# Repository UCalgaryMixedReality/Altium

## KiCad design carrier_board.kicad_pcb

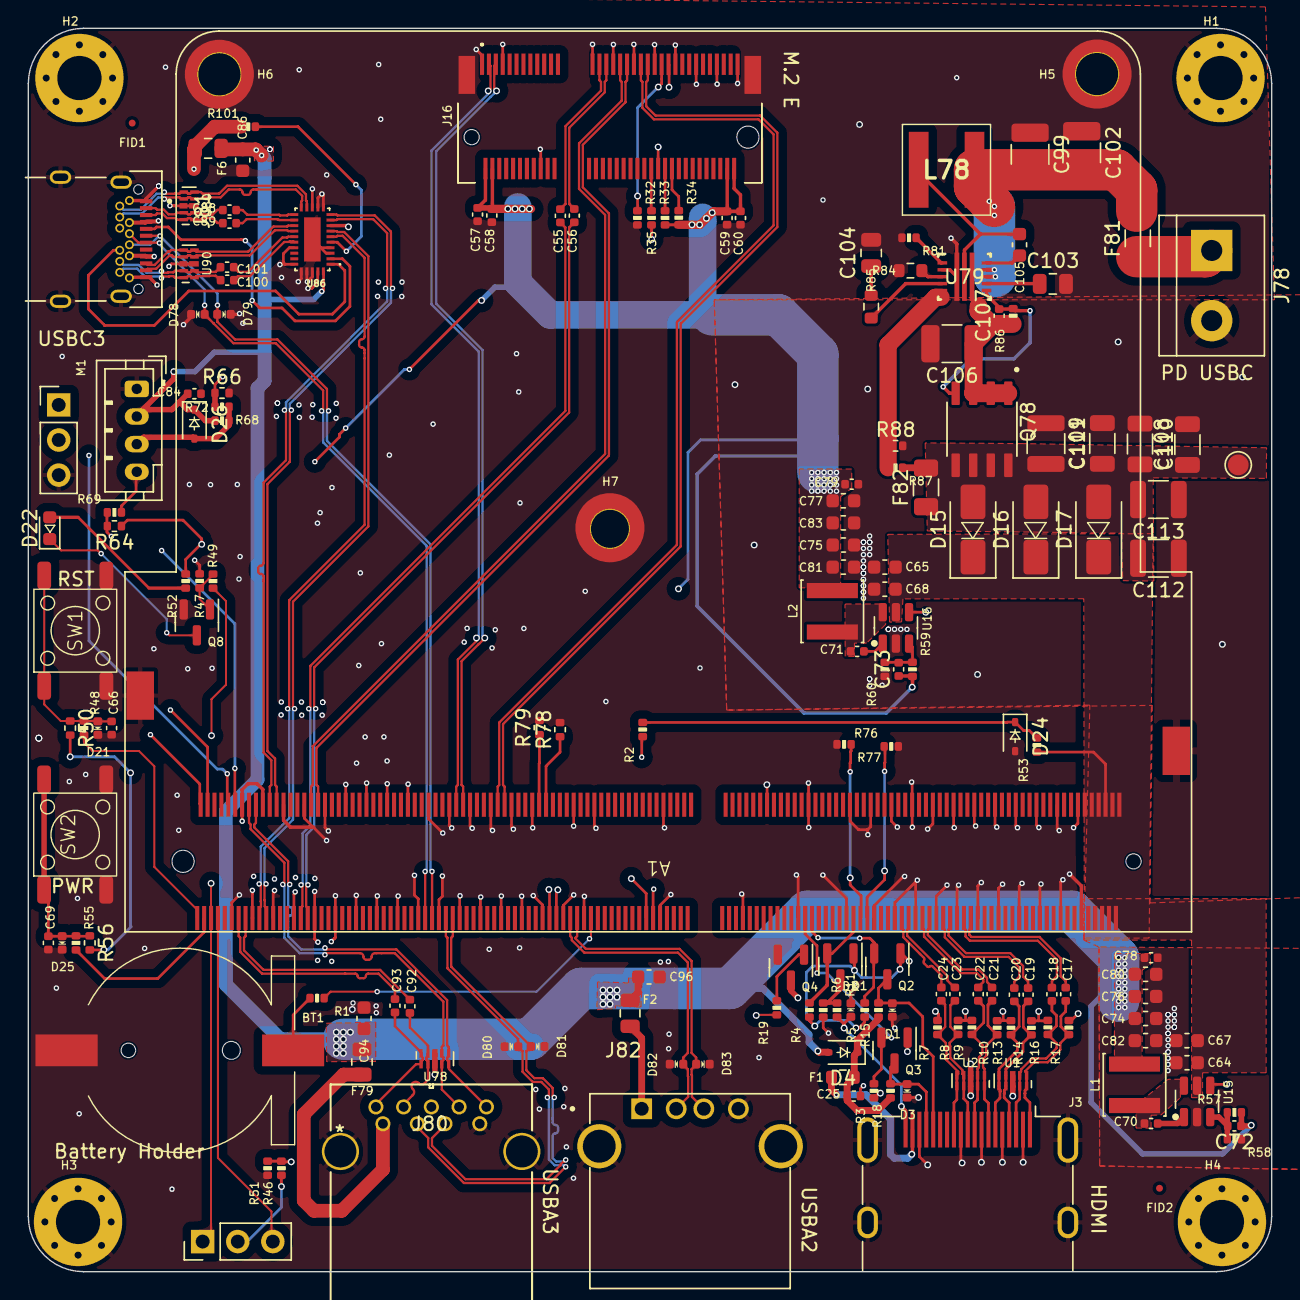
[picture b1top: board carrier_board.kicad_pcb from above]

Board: 4 copper layers, 90.0 x 90.0 mm, 175 parts (0 on the bottom side), 126 nets.

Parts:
A1: LattePanda_Mu; LattePanda_Module_H8.0mm_Horizontal
BT1: Battery_Cell; Battery_Holder_CR1220_S8411-45R
C17, C18, C19, C20, C21, C22, C23, C24, C25, C58, C60, C70, C71, C78, C79, C84, C88, C89, C92, C93, C100, C101: 100nF/50V; C_0402_1005Metric
C55, C56: 220nF/50V; C_0402_1005Metric
C57, C59: 10uF/10V; C_0402_1005Metric
C64, C65, C67, C68, C74, C75, C76, C77, C80, C81, C82, C83, C86, C94, C96: 22uF/10V; C_0603_1608Metric
C66, C69: 1uF/16V; C_0402_1005Metric
C72, C73: 12pF/50V; C_0402_1005Metric
C99, C102: 22uF; C_1210_3225Metric_Pad1.33x2.70mm_HandSolder
C103: 4.7uF; C_0805_2012Metric
C104: 1nF; C_0805_2012Metric
C105: 150nF; C_0603_1608Metric
C106: 10uF; C_1210_3225Metric_Pad1.33x2.70mm_HandSolder
C107: 22nF; C_0402_1005Metric
C108, C109, C110: 4.7uF; C_1206_3216Metric
C111, C112, C113: 22uF; C_1210_3225Metric
D1, D2, D3, D21, D25, D78, D79, D80, D81, D82, D83: ESD5V0B03; D_0402_1005Metric
D4, D26: 1N5819WS; D_SOD-323
D15, D16, D17: SS54; D_SMA
D22: LED_G; LED_0603_1608Metric
D24: 3V3 Izt=5mA; D_SOD-323
F1: 6V/50mA; R_0603_1608Metric
F2: 6V/1A; Fuse_0805_2012Metric
F6: 6V/2A; Fuse_0805_2012Metric
F79: 6V/2A; R_0805_2012Metric
F81: 32V/6A; Fuse_1206_3216Metric
F82: Fuse; Fuse_1206_3216Metric
FID1, FID2: Fiducial; Fiducial_0.5mm_Mask1mm
H1, H2, H3, H4: MountingHole_Pad; MountingHole_3.2mm_M3_Pad_Via
H5, H6: MountingHole_Pad; MountingHole_3mm_M2_Pad_TopOnly
H7: MountingHole_M2.0; MountingHole_2.7mm_M2_Pad_TopOnly
J1: Conn_01x03_Pin; PinHeader_1x03_P2.54mm_Vertical
J3: HDMI_A; HDMI_A_Molex_208658-1001_Horizontal
J16: Bus_M.2_Socket_E; PCIe_M.2_Connectors_P=0.5mm_H=4.2mm_KeyE
J78: Screw_Terminal_01x02; TerminalBlock_bornier-2_P5.08mm
J80: 0483930003; 484050003_MOL
J81: DX07S024JJ3R1300; AMPHENOL_GSB3CA11310DSHR
J82: USB-A1HSW6; OST_USB-A1HSW6
JP1: Jumper_3_Bridged12; PinHeader_1x03_P2.54mm_Vertical
L1, L2: 2.2uH/4.3A; L_Sunlord_SWPA4020S
L78: 560nF; XAL6030561MEB
M1: Fan_4pin; JST_PH_B4B-PH-K_1x04_P2.00mm_Vertical
Q1, Q8: 2N7002; SOT-23
Q2, Q3, Q4: 2SK3018; SOT-23
Q78: SI4427BDY-T1-E3; SOIC127P600X175-8N
R1, R11, R47: 1K/1%; R_0402_1005Metric
R2, R34, R35, R49, R50, R56, R58, R78, R79: 10K/1%; R_0402_1005Metric
R3, R5, R15, R18, R19, R52, R53: 2.2K/1%; R_0402_1005Metric
R4: 1M/1%; R_0402_1005Metric
R6, R59, R66, R68: 21.5K/1%; R_0402_1005Metric
R7, R8, R9, R10, R13, R14, R16, R17: 470R/1%; R_0402_1005Metric
R32, R33: 0R/1%; R_0402_1005Metric
R46, R48, R55, R69: 100R/1%; R_0402_1005Metric
R51, R76, R77: 100K/1%; R_0402_1005Metric
R57: 75K/1%; R_0402_1005Metric
R60, R64, R72: 4.7K/1%; R_0402_1005Metric
R81: 140k; R_0402_1005Metric
R84: 56.2k; R_0603_1608Metric
R85: 28.7k; R_0603_1608Metric
R86: 178k; R_0402_1005Metric
R87: 732k; R_0402_1005Metric
R88: 80.6k; R_0402_1005Metric
R101: 900k; R_0402_1005Metric
SW1, SW2: SW_Push; SW_Push_6x6x6
TP16: TestPoint; TestPoint_Pad_D1.5mm
U1, U2: TPAZ1023-04F; Diodes_UDFN-10_1.0x2.5mm_P0.5mm
U15, U16: SY8253ADC; TSOT-23-6
U78, U80, U90: ULC0524P; Diodes_UDFN-10_1.0x2.5mm_P0.5mm
U79: TPS61178RNWR; RNW0013A
U86: HD3SS3220IRNHT; QFN40P450X250X80-31N120X320

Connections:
5V_HDMI_VCC: C25.1, D4.1 (K), F1.1, R15.1, R18.1
+3V3: C57.2, C58.2, C59.2, C60.2, C73.1, C75.2, C77.2, C79.1, C81.2, C83.2, J16.2 (3.3V), J16.4 (3.3V), J16.72 (3.3V), J16.74 (3.3V), L2.2, Q1.1 (G), Q2.1 (G), Q3.1 (G), R3.1, R4.1, R5.1, R34.2, R35.1, R50.2, R52.2, R56.2, R59.2, R64.1, U86.8 (VCC33)
+5V: C72.1, C74.2, C76.2, C78.1, C80.2, C82.2, C84.1, C86.2, C94.2, C96.1, D4.2 (A), D26.1 (K), F2.1, F6.1, F79.1, L1.2, M1.2 (+), R57.2, R72.1, U86.30 (VDD5)
+12V: C108.1, C109.1, C110.2, C111.2, C112.2, C113.2, D15.2 (A), D16.2 (A), D17.2 (A), F82.1, F82.2, Q78.5, Q78.6, Q78.7, Q78.8, R87.1, TP16.1
+BATT: A1.115 (VBAT), R1.1
/Fan_Temp/FAN_1_PWM: A1.2 (FAN1_PWM), R64.2, R69.1
/Fan_Temp/FAN_1_TAC: A1.4 (FAN1_TAC), R66.1, R68.2
/HDMI/DDC_SCL: D1.2 (A2), J3.15 (SCL), Q2.3 (D), R15.2
/HDMI/DDC_SDA: D3.2 (A2), J3.16 (SDA), Q3.3 (D), R18.2
/HDMI/DDI_B_DDC_SCL: A1.171 (DDIB_DDC_SCL), Q2.2 (S), R5.2
/HDMI/DDI_B_DDC_SDA: A1.169 (DDIB_DDC_SDA), Q3.2 (S), R3.2
/HDMI/DDI_B_HPD: A1.183 (DDIB_HPD), Q1.2 (S), R4.2
/HDMI/DDI_B_TX0+: A1.217 (DDIB_TX0+), C17.1
/HDMI/DDI_B_TX0-: A1.215 (DDIB_TX0-), C18.1
/HDMI/DDI_B_TX1+: A1.211 (DDIB_TX1+), C19.1
/HDMI/DDI_B_TX1-: A1.209 (DDIB_TX1-), C20.1
/HDMI/DDI_B_TX2+: A1.205 (DDIB_TX2+), C21.1
/HDMI/DDI_B_TX2-: A1.203 (DDIB_TX2-), C22.1
/HDMI/DDI_B_TX3+: A1.199 (DDIB_TX3+), C23.1
/HDMI/DDI_B_TX3-: A1.197 (DDIB_TX3-), C24.1
/HDMI/HPD: D2.2 (A2), J3.19 (HPD), R11.2
/HDMI/TMDS_CK+: C23.2, J3.10 (CK+), R8.1, U2.4, U2.7 (NC)
/HDMI/TMDS_CK-: C24.2, J3.12 (CK-), R7.1, U2.5, U2.6 (NC)
/HDMI/TMDS_D0+: C21.2, J3.7 (D0+), R10.1, U2.1, U2.10 (NC)
/HDMI/TMDS_D0-: C22.2, J3.9 (D0-), R9.1, U2.2, U2.9 (NC)
/HDMI/TMDS_D1+: C19.2, J3.4 (D1+), R14.1, U1.4, U1.7 (NC)
/HDMI/TMDS_D1-: C20.2, J3.6 (D1-), R13.1, U1.5, U1.6 (NC)
/HDMI/TMDS_D2+: C17.2, J3.1 (D2+), R17.1, U1.1, U1.10 (NC)
/HDMI/TMDS_D2-: C18.2, J3.3 (D2-), R16.1, U1.2, U1.9 (NC)
/LattePanda Module/HSIO_0_TX+: A1.13 (HSIO0_TX+), C93.1
/LattePanda Module/HSIO_0_TX-: A1.15 (HSIO0_TX-), C92.1
/LattePanda Module/HSIO_1_TX+: A1.19 (HSIO1_TX+), U86.6 (TXP)
/LattePanda Module/HSIO_1_TX-: A1.21 (HSIO1_TX-), U86.7 (TXN)
/LattePanda Module/HSIO_3_RX+: A1.34 (HSIO3_RX+), J16.41 (PERp0)
/LattePanda Module/HSIO_3_RX-: A1.36 (HSIO3_RX-), J16.43 (PERn0)
/LattePanda Module/HSIO_3_TX+: A1.31 (HSIO3_TX+), C55.1
/LattePanda Module/HSIO_3_TX-: A1.33 (HSIO3_TX-), C56.1
/LattePanda Module/REFCLK3+: A1.88 (REFCLK3+), J16.47 (REFCLKp0)
/LattePanda Module/REFCLK3-: A1.90 (REFCLK3-), J16.49 (REFCLKn0)
/LattePanda Module/SLS_S3: A1.7 (SLS_S3), JP1.3 (B)
/LattePanda Module/SUSCLK_WIFI: A1.131 (SUSCLK), R33.2
/LattePanda Module/USB_2_P7+: A1.76 (USB2_P7+), J16.3 (USB_D+)
/LattePanda Module/USB_2_P7-: A1.78 (USB2_P7-), J16.5 (USB_D-)
/LattePanda Module/~PWR_SW: A1.1 (~PWRBTN), R48.2
/LattePanda Module/~RST_SW: A1.3 (~RSTBTN), R55.2
/M.2 E&M Key/CON_PCIE_TX_0+: C55.2, J16.35 (PETp0)
/M.2 E&M Key/CON_PCIE_TX_0-: C56.2, J16.37 (PETn0)
/M.2 E&M Key/~CLKREQE: J16.53 (~CLKREQ0), R32.1
/PSU/PWR_EN: R46.2, R51.2, U15.4 (EN), U16.4 (EN)
/USB2.0&USB3.0/CON_USB1_D_N: A1.109 (USB2_P5-), D82.2 (A2), J82.2 (D-)
/USB2.0&USB3.0/CON_USB1_D_P: A1.111 (USB2_P5+), D83.2 (A2), J82.3 (D+)
/USB2.0&USB3.0/CON_USB3_D_N: A1.73 (USB2_P2-), D80.2 (A2), J80.2 (D-)
/USB2.0&USB3.0/CON_USB3_D_P: A1.75 (USB2_P2+), D81.2 (A2), J80.3 (D+)
/USB2.0&USB3.0/CON_USB3_SSRX_N: A1.18 (HSIO0_RX-), J80.5 (STDA_SSRX-), U78.5, U78.6 (NC)
/USB2.0&USB3.0/CON_USB3_SSRX_P: A1.16 (HSIO0_RX+), J80.6 (STDA_SSRX+), U78.4, U78.7 (NC)
/USB2.0&USB3.0/CON_USB3_SSTX_N: C92.2, J80.8 (STDA_SSTX-), U78.2, U78.9 (NC)
/USB2.0&USB3.0/CON_USB3_SSTX_P: C93.2, J80.9 (STDA_SSTX+), U78.1, U78.10 (NC)
/USB2.0&USB3.0/CON_USB4_D_N: A1.67 (USB2_P1-), D78.2 (A2), J81.A7 (DA-), J81.B7 (DB-)
/USB2.0&USB3.0/CON_USB4_D_P: A1.69 (USB2_P1+), D79.2 (A2), J81.A6 (DA+), J81.B6 (DB+)
/USB2.0&USB3.0/CON_USB4_SSRX_N: A1.24 (HSIO1_RX-), U86.10 (RXN)
/USB2.0&USB3.0/CON_USB4_SSRX_P: A1.22 (HSIO1_RX+), U86.9 (RXP)
/USB2.0&USB3.0/CON_USBC_SSRX1_N: J81.B11 (RX1+), U80.5, U80.6 (NC), U86.14 (RX1N)
/USB2.0&USB3.0/CON_USBC_SSRX1_P: J81.B10 (RX1-), U80.4, U80.7 (NC), U86.15 (RX1P)
/USB2.0&USB3.0/CON_USBC_SSRX2_N: J81.A10 (RX2-), U86.18 (RX2N), U90.5, U90.6 (NC)
/USB2.0&USB3.0/CON_USBC_SSRX2_P: J81.A11 (RX2+), U86.19 (RX2P), U90.4, U90.7 (NC)
/USB2.0&USB3.0/CON_USBC_SSTX1_N: C88.1, J81.A2 (TX1+), U80.2, U80.9 (NC)
/USB2.0&USB3.0/CON_USBC_SSTX1_P: C89.1, J81.A3 (TX1-), U80.1, U80.10 (NC)
/USB2.0&USB3.0/CON_USBC_SSTX2_N: C101.2, J81.B3 (TX2-), U90.2, U90.9 (NC)
/USB2.0&USB3.0/CON_USBC_SSTX2_P: C100.2, J81.B2 (TX2+), U90.1, U90.10 (NC)
/~PLT_RST: A1.105 (~PLTRST), J16.52 (~PERST0)
/~PWR_LED/~PSON: A1.5 (SLS_S0), JP1.1 (A), R19.1, R47.1
/~WAKE: A1.103 (~WAKE), J16.55 (~PEWAKE0)
GND: A1.11 (GND), A1.14 (GND), A1.17 (GND), A1.20 (GND), A1.23 (GND), A1.26 (GND), A1.29 (GND), A1.32 (GND), A1.35 (GND), A1.38 (GND), A1.41 (GND), A1.44 (GND), A1.47 (GND), A1.50 (GND), A1.53 (GND), A1.56 (GND), A1.59 (GND), A1.62 (GND), A1.65 (GND), A1.68 (GND), A1.71 (GND), A1.74 (GND), A1.77 (GND), A1.80 (GND), A1.83 (GND), A1.86 (GND), A1.89 (GND), A1.92 (GND), A1.95 (GND), A1.98 (GND), A1.101 (GND), A1.107 (GND), A1.110 (GND), A1.113 (GND), A1.116 (GND), A1.135 (GND), A1.136 (GND), A1.151 (GND), A1.158 (GND), A1.167 (GND), A1.170 (GND), A1.181 (GND), A1.182 (GND), A1.188 (GND), A1.189 (GND), A1.194 (GND), A1.195 (GND), A1.200 (GND), A1.201 (GND), A1.206 (GND), A1.207 (GND), A1.212 (GND), A1.213 (GND), A1.218 (GND), A1.219 (GND), A1.224 (GND), A1.225 (GND), A1.230 (GND), A1.231 (GND), A1.236 (GND), A1.237 (GND), A1.242 (GND), A1.243 (GND), A1.248 (GND), A1.249 (GND), A1.MP (Mountinge_Pads), BT1.2 (-), C25.2, C57.1, C58.1, C59.1, C60.1, C64.1, C65.1, C66.2, C67.1, C68.1, C69.2, C74.1, C75.1, C76.1, C77.1, C78.2, C79.2, C80.1, C81.1, C82.1, C83.1, C84.2, C86.1, C94.1, C96.2, C99.1, C102.1, C103.2, C104.2, C106.2, C108.2, C109.2, C110.1, C111.1, C112.1, C113.1, D1.1 (A1), D2.1 (A1), D3.1 (A1), D21.1 (A1), D24.2 (A), D25.1 (A1), D78.1 (A1), D79.1 (A1), D80.1 (A1), D81.1 (A1), D82.1 (A1), D83.1 (A1), H1.1, H2.1, H3.1, H4.1, H5.1, H6.1, H7.1, J1.3, J3.2 (D2S), J3.5 (D1S), J3.8 (D0S), J3.11 (CKS), J3.17 (GND), J3.SH, J16.1 (GND), J16.7 (GND), J16.18 (GND), J16.33 (GND), J16.39 (GND), J16.45 (GND), J16.51 (GND), J16.57 (GND), J16.63 (GND), J16.69 (GND), J16.75 (GND), J16.MP1, J16.MP2, J78.2, J80.4 (GND), J80.7 (GND_DRAIN), J80.10, J80.11, J81.A1 (GNDA), J81.A12 (GNDA__1), J81.B1 (GNDB), J81.B12 (GNDB__1), J81.SH1, J81.SH3, J81.SH4, J82.4 (GND), M1.1 (-), Q4.2 (S), Q8.2 (S), R6.2, R32.2, R49.1, R51.1, R58.1, R60.1, R66.2, R76.2, R77.2, R78.2, R79.2, R81.2, R84.2, R88.2, SW1.2, SW2.2, U1.3 (VSS), U1.8 (VSS), U2.3 (VSS), U2.8 (VSS), U15.2 (GND), U16.2 (GND), U78.3 (VSS), U78.8 (VSS), U79.2 (AGND), U79.6 (PGND), U80.3 (VSS), U80.8 (VSS), U86.3 (CURRENT_MODE), U86.4 (PORT), U86.11 (DIR), U86.12 (~ENN_MUX), U86.13 (GND), U86.22 (ADDR), U86.25 (SDA/OUT1), U86.26 (SCL/OUT2), U86.27 (ID), U86.28 (GND__1), U86.29 (~ENN_CC), U86.31 (EXP_PAD), U90.3 (VSS), U90.8 (VSS)
unnamed: A1.12 (SIO_UART_RX), J1.2
unnamed: A1.10 (SIO_UART_TX), J1.1
unnamed: A1.187 (TCP0_HPD), R76.1
unnamed: A1.185 (TCP1_HPD), R77.1
unnamed: A1.133 (~BIOS_SEL), R2.1
unnamed: A1.100 (~CLKREQ3), R79.1
unnamed: A1.102 (~CLKREQ4), R78.1
unnamed: BT1.1 (+), R1.2
unnamed: C104.1, R85.2
unnamed: C66.1, D21.2 (A2), R48.1, R50.1, SW1.1
unnamed: D22.2 (A), R52.1
unnamed: D22.1 (K), Q8.3 (D)
unnamed: C69.1, D25.2 (A2), R55.1, R56.1, SW2.1
unnamed: D26.2 (A), M1.3 (Tacho), R68.1, R72.2
unnamed: F1.2, J3.18 (+5V)
unnamed: J16.50 (SUSCLK), R33.1
unnamed: J16.56 (~W_DISABLE1), R34.1
unnamed: J16.54 (~W_DISABLE2), R35.2
unnamed: F81.1, J78.1
unnamed: F79.2, J80.1 (VBUS)
unnamed: F6.2, J81.A4 (A_VBUS), J81.A9 (A_VBUS__1), J81.B4 (B_VBUS), J81.B9 (B_VBUS__1), R101.1
unnamed: J81.A5 (CC1), U86.2 (CC1)
unnamed: J81.B5 (CC2), U86.1 (CC2)
unnamed: F2.2, J82.1 (VBUS)
unnamed: JP1.2 (C), R46.1
unnamed: M1.4 (PWM), R69.2
unnamed: Q1.3 (D), R6.1, R11.1
unnamed: Q4.3 (D), R7.2, R8.2, R9.2, R10.2, R13.2, R14.2, R16.2, R17.2
unnamed: Q4.1 (G), R19.2
unnamed: Q8.1 (G), R47.2, R49.2
unnamed: C70.2, U15.1 (BOOST)
unnamed: C72.2, R57.1, R58.2, U15.3 (FB)
unnamed: C70.1, L1.1, U15.6 (SW)
unnamed: C71.2, U16.1 (BOOST)
unnamed: C73.2, R59.1, R60.2, U16.3 (FB)
unnamed: C71.1, L2.1, U16.6 (SW)
unnamed: C105.2, U79.13 (BST)
unnamed: R85.1, U79.4 (COMP)
unnamed: C107.2, Q78.4, R86.2, U79.9 (DISDRV)
unnamed: C99.2, C102.2, F81.2, L78.1, U79.11 (EN), U79.12 (VIN)
unnamed: R87.2, R88.1, U79.5 (FB)
unnamed: R81.1, U79.1 (FREQ_SYNC)
unnamed: R84.1, U79.3 (ILIMIT)
unnamed: C105.1, L78.2, U79.7 (SW)
unnamed: C103.1, U79.10 (VCC)
unnamed: C106.1, C107.1, Q78.1, Q78.2, Q78.3, R86.1, U79.8 (VOUT)
unnamed: C88.2, U86.16 (TX1N)
unnamed: C89.2, U86.17 (TX1P)
unnamed: C101.1, U86.20 (TX2N)
unnamed: C100.1, U86.21 (TX2P)
unnamed: R101.2, U86.5 (VBUS_DET)
VDC: A1.250 (VIN), A1.251 (VIN), A1.252 (VIN), A1.253 (VIN), A1.254 (VIN), A1.255 (VIN), A1.256 (VIN), A1.257 (VIN), A1.258 (VIN), A1.259 (VIN), A1.260 (VIN), C64.2, C65.2, C67.2, C68.2, D15.1 (K), D16.1 (K), D17.1 (K), R53.1, U15.5 (VIN), U16.5 (VIN)
VPullup: D24.1 (K), R2.2, R53.2

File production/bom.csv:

Designator,Footprint,Quantity,Value,LCSC Part #
A1,LattePanda_Module_H8.0mm_Horizontal,1,LattePanda_Mu,
BT1,Battery_Holder_CR1220_S8411-45R,1,Battery_Cell,
"C100, C101, C17, C18, C19, C20, C21, C22, C23, C24, C25, C58, C60, C70, C71, C78, C79, C84, C88, C89, C92, C93",0402,22,100nF/50V,
"C102, C111, C112, C113, C99",1210,5,22uF,
C103,0805,1,4.7uF,
C104,0805,1,1nF,
C105,0603,1,150nF,
C106,1210,1,10uF,
C107,0402,1,22nF,
"C108, C109, C110",1206,3,4.7uF,
"C55, C56",0402,2,220nF/50V,
"C57, C59",0402,2,10uF/10V,
"C64, C65, C67, C68, C74, C75, C76, C77, C80, C81, C82, C83, C86, C94, C96",0603,15,22uF/10V,
"C66, C69",0402,2,1uF/16V,
"C72, C73",0402,2,12pF/50V,
"D1, D2, D21, D25, D3, D78, D79, D80, D81, D82, D83",0402,11,ESD5V0B03,
"D15, D16, D17",D_SMA,3,SS54,
D22,0603,1,LED_G,
D24,D_SOD-323,1,3V3 Izt=5mA,
"D26, D4",D_SOD-323,2,1N5819WS,
F1,0603,1,6V/50mA,
F2,0805,1,6V/1A,
"F6, F79",0805,2,6V/2A,
F81,1206,1,32V/6A,
F82,1206,1,Fuse,
"H5, H6",MountingHole_3mm_M2_Pad_TopOnly,2,MountingHole_Pad,
H7,MountingHole_2.7mm_M2_Pad_TopOnly,1,MountingHole_M2.0,
J1,PinHeader_1x03_P2.54mm_Vertical,1,Conn_01x03_Pin,
J16,PCIe_M.2_Connectors_P=0.5mm_H=4.2mm_KeyE,1,Bus_M.2_Socket_E,
J3,HDMI_A_Molex_208658-1001_Horizontal,1,HDMI_A,
J78,TerminalBlock_bornier-2_P5.08mm,1,Screw_Terminal_01x02,C394556
J80,484050003_MOL,1,0483930003,
J81,AMPHENOL_GSB3CA11310DSHR,1,DX07S024JJ3R1300,
J82,OST_USB-A1HSW6,1,USB-A1HSW6,
JP1,PinHeader_1x03_P2.54mm_Vertical,1,Jumper_3_Bridged12,
"L1, L2",L_Sunlord_SWPA4020S,2,2.2uH/4.3A,
L78,XAL6030561MEB,1,560nF,
M1,JST_PH_B4B-PH-K_1x04_P2.00mm_Vertical,1,Fan_4pin,
"Q1, Q8",SOT-23,2,2N7002,
"Q2, Q3, Q4",SOT-23,3,2SK3018,
Q78,SOIC127P600X175-8N,1,SI4427BDY-T1-E3,
"R1, R11, R47",0402,3,1K/1%,
"R10, R13, R14, R16, R17, R7, R8, R9",0402,8,470R/1%,
R101,0402,1,900k,
"R15, R18, R19, R3, R5, R52, R53",0402,7,2.2K/1%,
"R2, R34, R35, R49, R50, R56, R58, R78, R79",0402,9,10K/1%,
"R32, R33",0402,2,0R/1%,
R4,0402,1,1M/1%,
"R46, R48, R55, R69",0402,4,100R/1%,
"R51, R76, R77",0402,3,100K/1%,
R57,0402,1,75K/1%,
"R59, R6, R66, R68",0402,4,21.5K/1%,
"R60, R64, R72",0402,3,4.7K/1%,
R81,0402,1,140k,
R84,0603,1,56.2k,
R85,0603,1,28.7k,
R86,0402,1,178k,
R87,0402,1,732k,
R88,0402,1,80.6k,
"SW1, SW2",SW_Push_6x6x6,2,SW_Push,
TP16,TestPoint_Pad_D1.5mm,1,TestPoint,
"U1, U2",Diodes_UDFN-10_1.0x2.5mm_P0.5mm,2,TPAZ1023-04F,
"U15, U16",TSOT-23-6,2,SY8253ADC,
"U78, U80, U90",Diodes_UDFN-10_1.0x2.5mm_P0.5mm,3,ULC0524P,
U79,RNW0013A,1,TPS61178RNWR,
U86,QFN40P450X250X80-31N120X320,1,HD3SS3220IRNHT,

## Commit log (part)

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2025-03-22 updated PCB and schematic
2025-03-22 Test delete in main
2025-03-22 Deleting all files from main
2025-03-22 Cleaning up buck converter branch
2025-03-22 cleaning up libraries branch
2025-03-22 Cleaning up boost branch
2025-03-22 cleaning up branch
2025-03-29 Committing the good copy of the boost converter
2025-03-29 Committing the good copy again
2025-03-29 Adding PCB and schematic documents to the altium project
2025-03-29 Trying to commit the good copy of the boost converter
2025-03-29 Update board shape
    Added project output hooks
    Added polygon pour layers
2025-03-29 Updated the configuration in Gerber files to ensure they upload correctly onto JLCPCB
2025-03-29 Added mechanical layer 15 on the IC and screw connector
    Added a molex connector to the PCB
    Added the integrated library
2025-03-29 Reorganized the folders
2025-04-13 Folder Re-structuring
2025-04-13 Adding unversioned files which did not get included in the previous commit
2025-04-28 Completed Buck converter PCB (with zipped fabrication output files included). Just attached the zipped fabrication output file into JLCPCB to order the completed PCB
2025-05-24 fixed the pcb by correcting the capacitor and changing the input terminal to a screw terminal
2025-05-29 added the corrected gerber file and reorganized the file
2025-05-30 updated the output job files
2025-07-05 Project commimt of carrier pcb with boost and battery supply terminals
    Project commit of carrier pcb with boost and battery supply terminals
